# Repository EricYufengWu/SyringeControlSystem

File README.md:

# Syringe Control System for Soft Robot Actuators

## General Info

This repository hosts code, PCB designs, and other results from my undergraduate independent research course. This research is supervised by Professor Chris Rogers at Tufts University.

The goal of the research is to develop a low-cost, modular pneumatic system that controls soft actuators using a linear actuator and a medical syringe. If time allows, I will also try to perform a well-rounded comparison between my new system and traditional controlling methods like [this one.](https://softroboticstoolkit.com/book/control-board). For now, the system is named "Syringe Control System", or SCS in short.

I would like to thank Professor Chris Rogers, Part-time Lecturer Brandon Stafford, and many other people from [Tufts Center for Engineering Education and Outreach](https://ceeo.tufts.edu/) and [Tufts Nolop FAST Facility](https://nolop.org/) for making this project possible.

Scroll down for pictures, demos, and complete building instructions.

Questions? Email yufeng.wu@tufts.edu and I will try to get back to you ASAP. I would also love to hear feedback or suggestions on how I can improve the current system.

## Images & Demos

Check out my presentation video on Youtube: https://youtu.be/lQ8lNfzFreA

## BOM & Links

Click [here](https://docs.google.com/spreadsheets/d/1QlE3OmNmio2WvQ-pDKSaTucrADuNShoU5-5D75yimro/edit?usp=sharing) for the complete bill of materials.

Click [here](https://grabcad.com/library/linear-syringe-system-for-controlling-soft-robot-actuators-1/details?folder_id=8379164) for the 3D-printed components in STL, STEP, and SolidWorks format.

You can also view the 3D-model online through [here](https://autode.sk/2SUinZA)

Get the latest Gerber package and original KiCAD files (with custom libraries) under the "PCB" folder.

## Building Instructions

A full manual, including instructions on BOM, 3D-printing, ordering PCB, mechanical assembly, coding, and operation, can be found [here](https://github.com/EricYufengWu/PneumaticSyringeSystem/blob/master/Documentation/SCS_Manual_v3.1.pdf) in PDF. 

## Using The Code

Please see "Arduino_TeensyLC" for some simple demo code I wrote for the system.

Follow the instruction on the [PJRC Website](https://www.pjrc.com/teensy/teensyLC.html) to set up your Teensy LC. Similarly, go to the [Arduino Website](https://www.arduino.cc/en/Guide/ArduinoNano) if you are setting up an Arduino Nano as the Master Unit.

Upload "mid_master_TC" to the Teensy LC on each of your units. For every new unit, you will need to change the I2C slave address on line 41. If you are not sure what address values you can use, check out [this helpful list](https://learn.adafruit.com/i2c-addresses/the-list) form Adafruit. In the code, you can also tune the gain constants for the closed-loop control system in line 32 - 38. They have not been fine tuned yet, but for now they seem to work with little to no problem. If you end up finding better constant values, please do not hesitate to share it with me!

After you upload the code to a control unit, the unit should be operational in manual mode, i.e. after connecting the unit to 12V motor and 5V logic power, you should be able to control the unit using the built'in buttons. You should also be able to view the current pressure and positional data if you access the Teensy LC using a serial manitor on your computer.

Upload "top_master_nano.ino" to your arduino Nano as the master unit. You can use the serial input to send command to and get data from any designated unit in the I2C bus.

For more detailed instruciton, please refer to the instruction manual.

BEFORE YOU PROCEED: Please read the next section about the limitations of the SCS as well as things to keep in mind during its operation. 

## Limitations and Precautions
I2C protocol is capable of connecting more than 100 slaves at once. However, for the current version, it is recommended that you do not connect more than 8 units to the same master unit at the same time. This is due to the current rating of the wires used in the design. Future development will focus on how to tackle this issue.

Although the system uses Sparkfun's Qwiic system to communicaate with the units via I2C, it is currently NOT compatible with other boards on the Qwiic system: The SCS uses 5V on its logic line to power the Teensy LC, whereas the real Qwiic system uses 3.3V to power the sensors. Connecting other 3.3V sensors to the SCS system could permanently damage your sensors!

Keep in mind that although the system proves to be safe to operate, the stability of the system has not been so thoroughly tested. This mostly means that certain components might accidentally malfunction or get heated up.

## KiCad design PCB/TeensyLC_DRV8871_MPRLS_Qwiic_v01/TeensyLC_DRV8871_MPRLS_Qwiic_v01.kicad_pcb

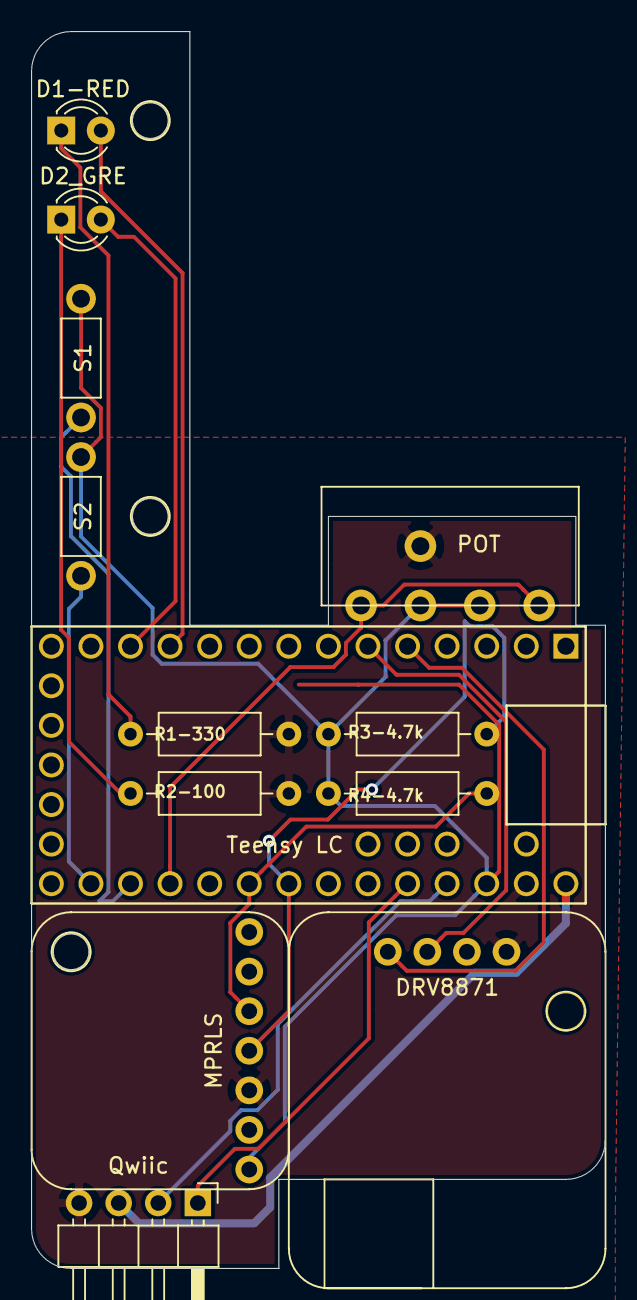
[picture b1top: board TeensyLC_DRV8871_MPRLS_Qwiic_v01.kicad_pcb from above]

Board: 2 copper layers, 36.8 x 79.4 mm, 12 parts (0 on the bottom side), 6 nets.

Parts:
D1-RED, D2_GRE: LED; LED_D3.0mm
DRV8871: Adafruit_DRV8871
MPRLS: Adafruit_MPRLS; Adafruit MPRLS
POT: R_POT_US; Linear_POT
Qwiic: Sparkfun_Qwiic_Adapter; Sparkfun_Qwiic_Breakout
R1-330, R2-100: 220Ω; R_Axial_DIN0207_L6.3mm_D2.5mm_P10.16mm_Horizontal
R3-4.7k, R4-4.7k: 4.7kΩ; R_Axial_DIN0207_L6.3mm_D2.5mm_P10.16mm_Horizontal
S1, S2: Push_SW

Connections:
/3V3: MPRLS.1, POT.1, R3-4.7k.1, R4-4.7k.1, S1.2, S2.2
/SCL0: MPRLS.4, R3-4.7k.2
/SDA0: MPRLS.5, R4-4.7k.2
GND: DRV8871.4, MPRLS.3, POT.3, Qwiic.4, R1-330.2, R2-100.2
unnamed: D1-RED.1, R1-330.1
unnamed: D2_GRE.1, R2-100.1

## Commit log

2020-03-31 second commit
2020-04-02 updated code and journal
2020-04-23 V3 System Test
2020-04-23 updated minmaster code for manual
2020-04-23 updated journal
2020-04-25 version 3.1 models and journal
2020-04-25 Revert "version 3.1 models and journal"
    This reverts commit 977644da9f5aa0aca8d70ec5670a792cd3697fd3.
2020-04-25 rm large files
2020-04-26 remove large file
2020-04-26 mapping pot to position
2020-04-26 updated get_data, changed to struct array
2020-04-26 communication back-and-forth between mid and top master
2020-04-27 added move-to-loc, get-address, get-data
2020-04-27 cleaned up uneccesary files
2020-04-27 finished code for V3.1, fully functional serial interface at master controller
2020-05-04 image test
2020-05-04 updated PCB
2020-05-05 moved CAD files out of the repo
2020-05-17 added instruction manual
2020-05-19 Correct erroneous title
2020-06-09 Set theme jekyll-theme-minimal
